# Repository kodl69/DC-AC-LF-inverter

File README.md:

# DC-AC-LF-inverter
software and hardware for modular DC/AC power inverter

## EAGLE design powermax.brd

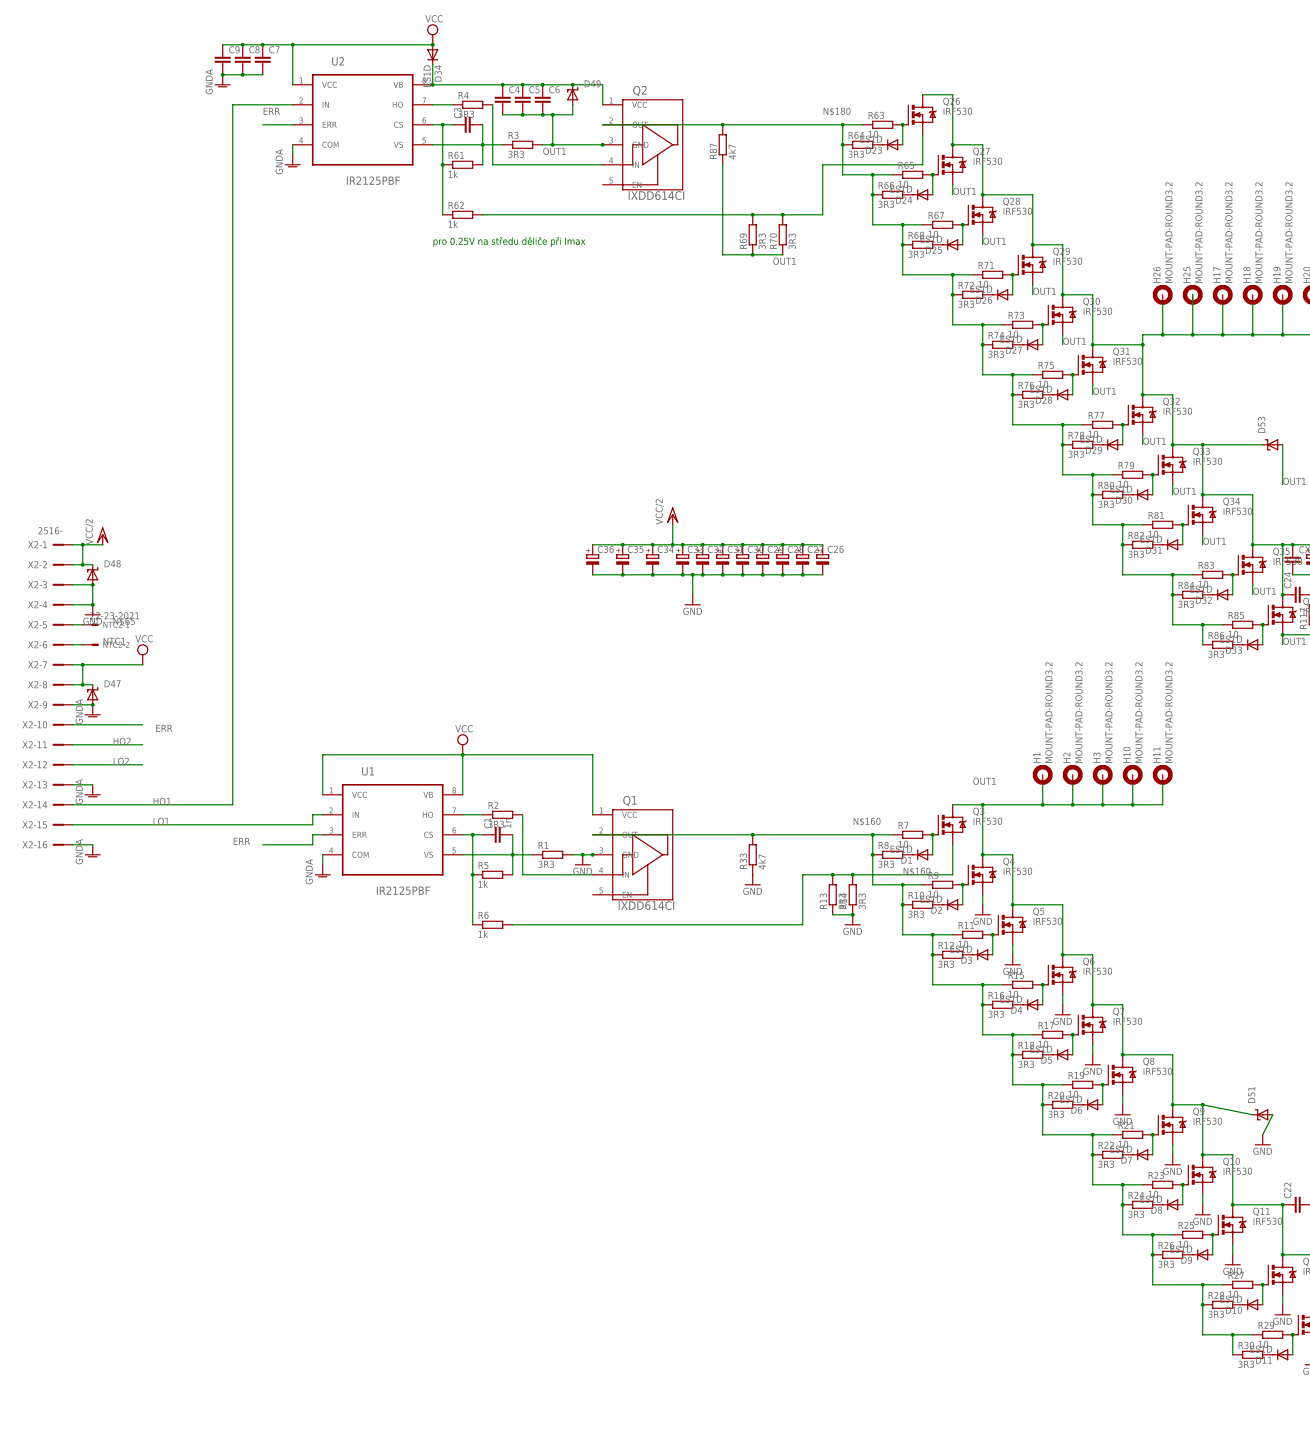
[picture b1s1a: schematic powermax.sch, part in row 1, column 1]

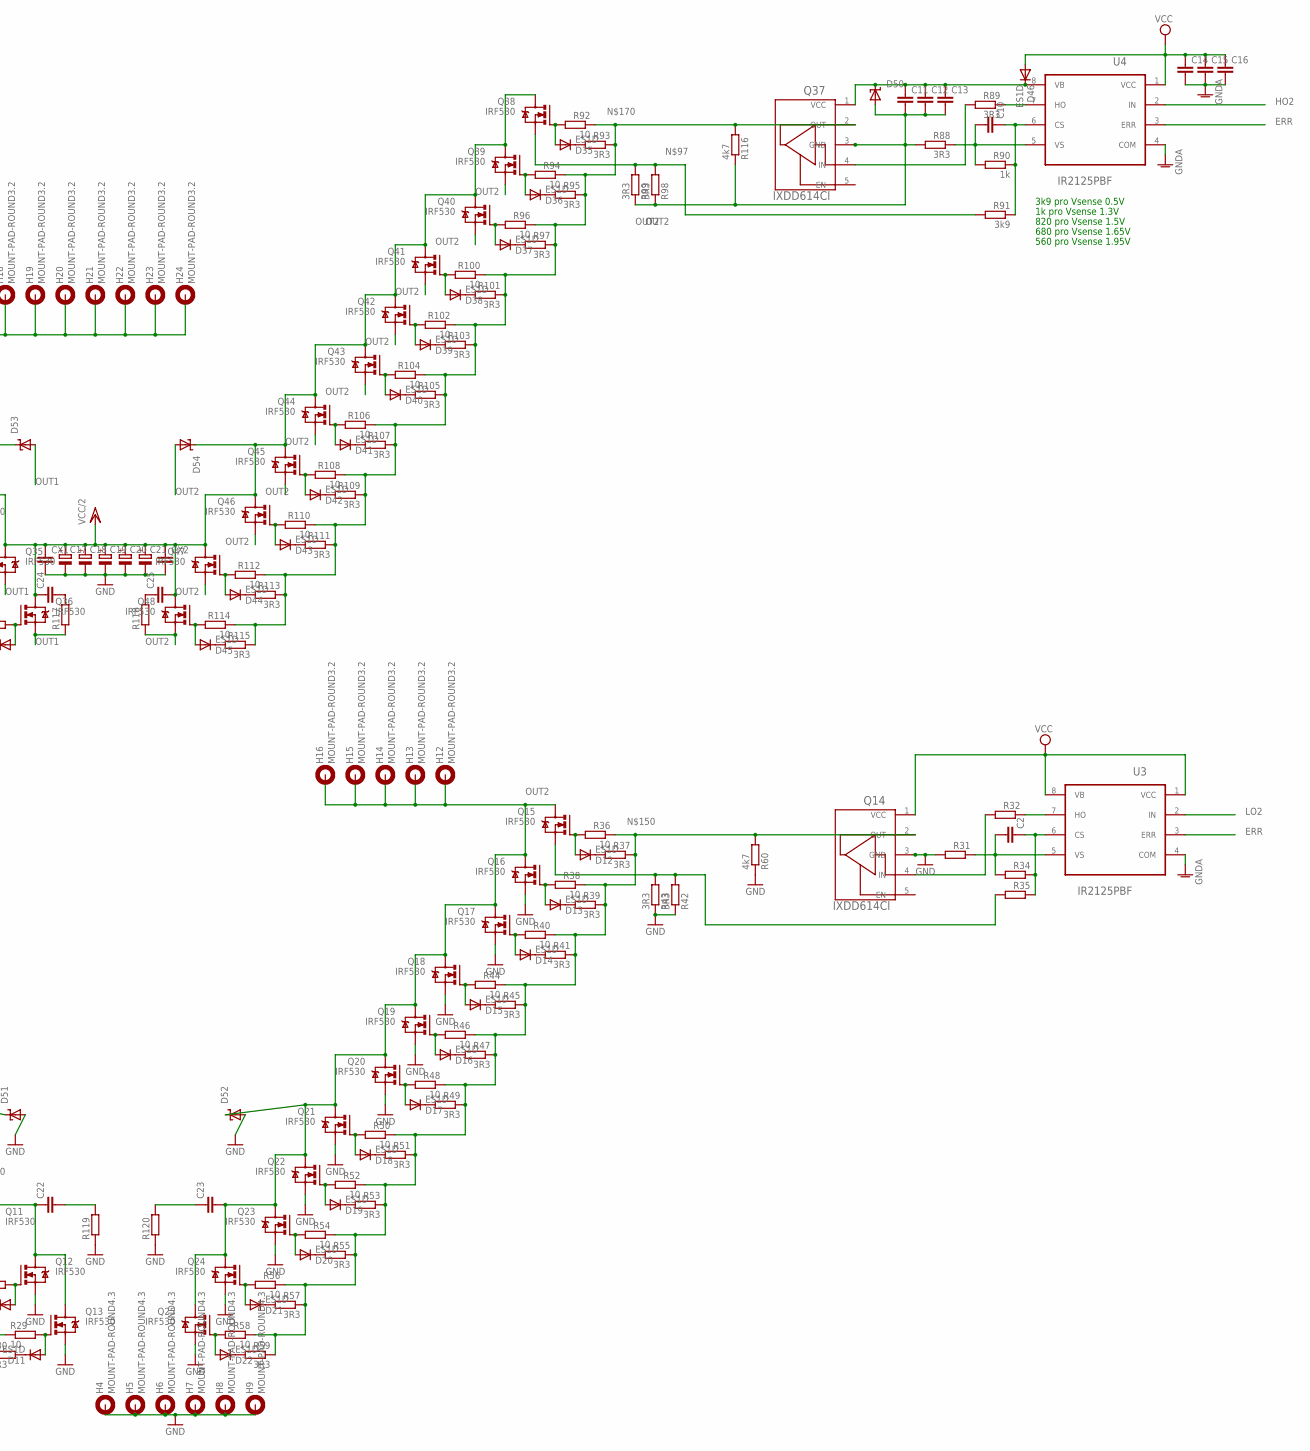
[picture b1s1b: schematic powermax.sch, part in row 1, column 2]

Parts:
C1: 1n; C0805
C2, C3, C10: C-EUC0805; C0805
C4, C5, C6, C7, C8, C9, C11, C12, C13, C14, C15, C16: C-EUC1210; C1210
C17, C18, C19, C20, C21: CPOL-EUE10-35; EB35D
C22, C23, C24, C25: C-EU225-113X268; C225-113X268
C26, C27, C28, C29, C30, C31, C32, C33, C34, C35, C36: CPOL-EUE7.5-18; E7,5-18
CX1, CX2: CXXC27B11; XC27B11
D1, D2, D3, D4, D5, D6, D7, D8, D9, D10, D11, D12, D13, D14, D15, D16, D17, D18, D19, D20, D21, D22, D23, D24, D25, D26, D27, D28, D29, D30, D31, D32, D33, D34, D35, D36, D37, D38, D39, D40, D41, D42, D43, D44, D45, D46: ES1D; SOD80C
D47, D48, D49, D50, D51, D52, D53, D54: SUPPRESSOR-SMBJ; SMBJ
H1, H2, H3, H10, H11, H12, H13, H14, H15, H16, H17, H18, H19, H20, H21, H22, H23, H24, H25, H26: MOUNT-PAD-ROUND3.2; 3,2-PAD
H4, H5, H6, H7, H8, H9: MOUNT-PAD-ROUND4.3; 4,3-PAD
NTC2: 22-23-2021
Q1, Q2, Q14, Q37: IXDD614CI; TO-220-5
Q3, Q4, Q5, Q6, Q7, Q8, Q9, Q10, Q11, Q12, Q13, Q15, Q16, Q17, Q18, Q19, Q20, Q21, Q22, Q23, Q24, Q25, Q26, Q27, Q28, Q29, Q30, Q31, Q32, Q33, Q34, Q35, Q36, Q38, Q39, Q40, Q41, Q42, Q43, Q44, Q45, Q46, Q47, Q48: IRF530; TO220BV
R1, R2, R3, R4, R8, R10, R12, R13, R14, R16, R18, R20, R22, R24, R26, R28, R30, R37, R39, R41, R42, R43, R45, R47, R49, R51, R53, R55, R57, R59, R64, R66, R68, R69, R70, R72, R74, R76, R78, R80, R82, R84, R86, R88, R89, R93, R95, R97, R98, R99, R101, R103, R105, R107, R109, R111, R113, R115: 3R3; R0805
R5, R6, R61, R62, R90: 1k; R0805
R7, R9, R11, R15, R17, R19, R21, R23, R25, R27, R29, R36, R38, R40, R44, R46, R48, R50, R52, R54, R56, R58, R63, R65, R67, R71, R73, R75, R77, R79, R81, R83, R85, R92, R94, R96, R100, R102, R104, R106, R108, R110, R112, R114: 10; R0805
R31, R32, R34, R35: R-EU_R0805; R0805
R33, R60, R87, R116: 4k7; R0805
R91: 3k9; R0805
R117, R118, R119, R120: R-EU_0411/15; 0411/15
U1, U2, U3, U4: IR2125PBF; DIP254P762X533-8
X2: 2516-; PAK100/2500-16

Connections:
ERR: U1.3 (ERR), U2.3 (ERR), U3.3 (ERR), U4.3 (ERR), X2.10
GND: C17.-, C18.-, C19.-, C20.-, C21.-, C26.-, C27.-, C28.-, C29.-, C30.-, C31.-, C32.-, C33.-, C34.-, C35.-, C36.-, CX1.2, CX2.2, D48.A, D51.A, D52.A, H4.B4,3, H5.B4,3, H6.B4,3, H7.B4,3, H8.B4,3, H9.B4,3, Q1.3 (GND), Q4.S, Q5.S, Q6.S, Q7.S, Q8.S, Q9.S, Q10.S, Q11.S, Q12.S, Q13.S, Q14.3 (GND), Q16.S, Q17.S, Q18.S, Q19.S, Q20.S, Q21.S, Q22.S, Q23.S, Q24.S, Q25.S, R1.2, R13.1, R14.1, R31.2, R33.1, R42.1, R43.1, R60.1, R119.1, R120.1, X2.3, X2.4
GNDA: C7.2, C8.2, C9.2, C14.2, C15.2, C16.2, D47.A, U1.4 (COM), U2.4 (COM), U3.4 (COM), U4.4 (COM), X2.9, X2.13, X2.16
HO1: U2.2 (IN), X2.14
HO2: U4.2 (IN), X2.11
LO1: U1.2 (IN), X2.15
LO2: U3.2 (IN), X2.12
unnamed: C1.2, R1.1, R5.2, U1.5 (VS)
unnamed: Q1.4 (IN), R2.2
unnamed: R2.1, U1.7 (HO)
unnamed: C2.2, R31.1, R34.2, U3.5 (VS)
unnamed: D2.A, Q4.G, R9.2
unnamed: C1.1, R5.1, R6.1, U1.6 (CS)
unnamed: D1.A, Q3.G, R7.2
unnamed: D1.C, R8.2
unnamed: D2.C, R10.2
unnamed: Q14.4 (IN), R32.2
unnamed: R32.1, U3.7 (HO)
unnamed: C4.1, C5.1, C6.1, D34.C, D49.C, Q2.1 (VCC), U2.8 (VB)
unnamed: D3.A, Q5.G, R11.2
unnamed: D3.C, R12.2
unnamed: C2.1, R34.1, R35.1, U3.6 (CS)
unnamed: Q3.S, R6.2, R13.2, R14.2
unnamed: D12.A, Q15.G, R36.2
unnamed: D12.C, R37.2
unnamed: D4.A, Q6.G, R15.2
unnamed: D4.C, R16.2
unnamed: D5.A, Q7.G, R17.2
unnamed: D5.C, R18.2
unnamed: D13.A, Q16.G, R38.2
unnamed: D6.A, Q8.G, R19.2
unnamed: D6.C, R20.2
unnamed: D13.C, R39.2
unnamed: D7.A, Q9.G, R21.2
unnamed: D7.C, R22.2
unnamed: D8.A, Q10.G, R23.2
unnamed: D8.C, R24.2
unnamed: D9.A, Q11.G, R25.2
unnamed: D9.C, R26.2
unnamed: D14.A, Q17.G, R40.2
unnamed: D10.A, Q12.G, R27.2
unnamed: D10.C, R28.2
unnamed: D11.A, Q13.G, R29.2
unnamed: D11.C, R30.2
unnamed: D14.C, R41.2
unnamed: Q15.S, R35.2, R42.2, R43.2
unnamed: D15.A, Q18.G, R44.2
unnamed: D15.C, R45.2
unnamed: D16.A, Q19.G, R46.2
unnamed: D16.C, R47.2
unnamed: D17.A, Q20.G, R48.2
unnamed: D17.C, R49.2
unnamed: D18.A, Q21.G, R50.2
unnamed: D18.C, R51.2
unnamed: D19.A, Q22.G, R52.2
unnamed: D19.C, R53.2
unnamed: D20.A, Q23.G, R54.2
unnamed: D20.C, R55.2
unnamed: D21.A, Q24.G, R56.2
unnamed: D21.C, R57.2
unnamed: D22.A, Q25.G, R58.2
unnamed: D22.C, R59.2
unnamed: C3.2, R3.1, R61.2, U2.5 (VS)
unnamed: Q2.4 (IN), R4.2
unnamed: R4.1, U2.7 (HO)
unnamed: C3.1, R61.1, R62.1, U2.6 (CS)
unnamed: D23.A, Q26.G, R63.2
unnamed: D23.C, R64.2
unnamed: D24.A, Q27.G, R65.2
unnamed: D24.C, R66.2
unnamed: NTC2.1, X2.5
unnamed: D25.A, Q28.G, R67.2
unnamed: D25.C, R68.2
unnamed: Q26.S, R62.2, R69.2, R70.2
unnamed: D26.A, Q29.G, R71.2
unnamed: D26.C, R72.2
unnamed: D27.A, Q30.G, R73.2
unnamed: D27.C, R74.2
unnamed: D28.A, Q31.G, R75.2
unnamed: D28.C, R76.2
unnamed: D29.A, Q32.G, R77.2
unnamed: D29.C, R78.2
unnamed: D30.A, Q33.G, R79.2
unnamed: D30.C, R80.2
unnamed: D31.A, Q34.G, R81.2
unnamed: D31.C, R82.2
unnamed: D32.A, Q35.G, R83.2
unnamed: D32.C, R84.2
unnamed: D33.A, Q36.G, R85.2
unnamed: D33.C, R86.2
unnamed: C10.2, R88.1, R90.2, U4.5 (VS)
unnamed: Q37.4 (IN), R89.2
unnamed: R89.1, U4.7 (HO)
unnamed: C10.1, R90.1, R91.1, U4.6 (CS)
unnamed: D35.A, Q38.G, R92.2
unnamed: D35.C, R93.2
unnamed: D36.A, Q39.G, R94.2
unnamed: D36.C, R95.2
unnamed: D37.A, Q40.G, R96.2
unnamed: D37.C, R97.2
unnamed: Q38.S, R91.2, R98.2, R99.2
unnamed: D38.A, Q41.G, R100.2
unnamed: D38.C, R101.2
unnamed: D39.A, Q42.G, R102.2
unnamed: D39.C, R103.2
unnamed: D40.A, Q43.G, R104.2
unnamed: D40.C, R105.2
unnamed: D41.A, Q44.G, R106.2
unnamed: D41.C, R107.2
unnamed: D42.A, Q45.G, R108.2
unnamed: D42.C, R109.2
unnamed: D43.A, Q46.G, R110.2
unnamed: D43.C, R111.2
unnamed: D44.A, Q47.G, R112.2
unnamed: D44.C, R113.2
unnamed: D45.A, Q48.G, R114.2
unnamed: D45.C, R115.2
unnamed: C11.1, C12.1, C13.1, D46.C, D50.C, Q37.1 (VCC), U4.8 (VB)
unnamed: C24.2, R117.2
unnamed: C25.1, R118.2
unnamed: C22.2, R119.2
unnamed: C23.1, R120.2
unnamed: Q14.2 (OUT), R36.1, R37.1, R38.1, R39.1, R40.1, R41.1, R44.1, R45.1, R46.1, R47.1, R48.1, R49.1, R50.1, R51.1, R52.1, R53.1, R54.1, R55.1, R56.1, R57.1, R58.1, R59.1, R60.2
unnamed: Q1.2 (OUT), R7.1, R8.1, R9.1, R10.1, R11.1, R12.1, R15.1, R16.1, R17.1, R18.1, R19.1, R20.1, R21.1, R22.1, R23.1, R24.1, R25.1, R26.1, R27.1, R28.1, R29.1, R30.1, R33.2
unnamed: Q37.2 (OUT), R92.1, R93.1, R94.1, R95.1, R96.1, R97.1, R100.1, R101.1, R102.1, R103.1, R104.1, R105.1, R106.1, R107.1, R108.1, R109.1, R110.1, R111.1, R112.1, R113.1, R114.1, R115.1, R116.2
unnamed: Q2.2 (OUT), R63.1, R64.1, R65.1, R66.1, R67.1, R68.1, R71.1, R72.1, R73.1, R74.1, R75.1, R76.1, R77.1, R78.1, R79.1, R80.1, R81.1, R82.1, R83.1, R84.1, R85.1, R86.1, R87.2
NTC1: NTC2.2, X2.6
OUT1: C4.2, C5.2, C6.2, C22.1, D49.A, D51.C, D53.A, H1.B3,2, H2.B3,2, H3.B3,2, H10.B3,2, H11.B3,2, Q2.3 (GND), Q3.D, Q4.D, Q5.D, Q6.D, Q7.D, Q8.D, Q9.D, Q10.D, Q11.D, Q12.D, Q13.D, Q27.S, Q28.S, Q29.S, Q30.S, Q31.S, Q32.S, Q33.S, Q34.S, Q35.S, Q36.S, R3.2, R69.1, R70.1, R87.1, R117.1
OUT2: C11.2, C12.2, C13.2, C23.2, D50.A, D52.C, D54.A, H12.B3,2, H13.B3,2, H14.B3,2, H15.B3,2, H16.B3,2, Q15.D, Q16.D, Q17.D, Q18.D, Q19.D, Q20.D, Q21.D, Q22.D, Q23.D, Q24.D, Q25.D, Q37.3 (GND), Q39.S, Q40.S, Q41.S, Q42.S, Q43.S, Q44.S, Q45.S, Q46.S, Q47.S, Q48.S, R88.2, R98.1, R99.1, R116.1, R118.1
VCC: C7.1, C8.1, C9.1, C14.1, C15.1, C16.1, D34.A, D46.A, D47.C, Q1.1 (VCC), Q14.1 (VCC), U1.1 (VCC), U1.8 (VB), U2.1 (VCC), U3.1 (VCC), U3.8 (VB), U4.1 (VCC), X2.7, X2.8
VCC/2: C17.+, C18.+, C19.+, C20.+, C21.+, C24.1, C25.2, C26.+, C27.+, C28.+, C29.+, C30.+, C31.+, C32.+, C33.+, C34.+, C35.+, C36.+, CX1.1, CX2.1, D48.C, D53.C, D54.C, H17.B3,2, H18.B3,2, H19.B3,2, H20.B3,2, H21.B3,2, H22.B3,2, H23.B3,2, H24.B3,2, H26.B3,2, Q26.D, Q27.D, Q28.D, Q29.D, Q30.D, Q31.D, Q32.D, Q33.D, Q34.D, Q35.D, Q36.D, Q38.D, Q39.D, Q40.D, Q41.D, Q42.D, Q43.D, Q44.D, Q45.D, Q46.D, Q47.D, Q48.D, X2.1, X2.2

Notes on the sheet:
pro 0.25V na středu děliče při Imax
1k pro Vsense 1.3V
3k9 pro Vsense 0.5V
820 pro Vsense 1.5V
680 pro Vsense 1.65V
560 pro Vsense 1.95V

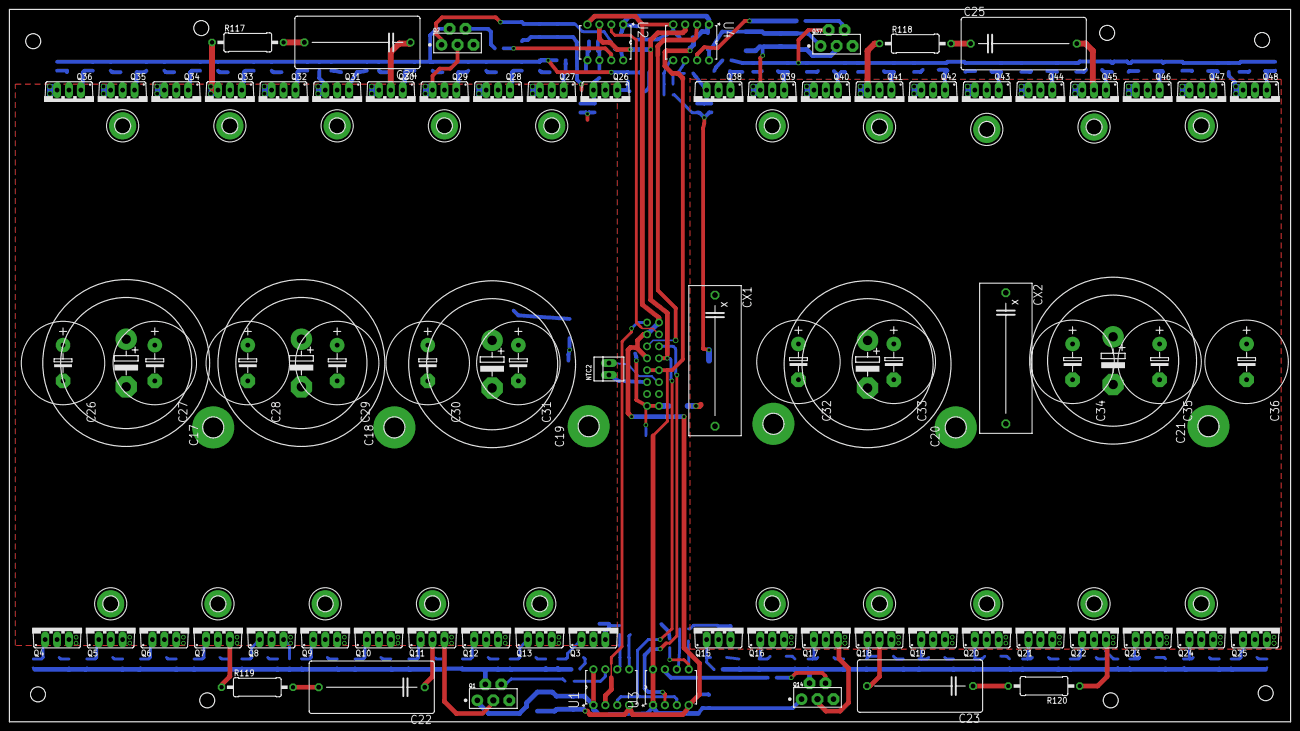
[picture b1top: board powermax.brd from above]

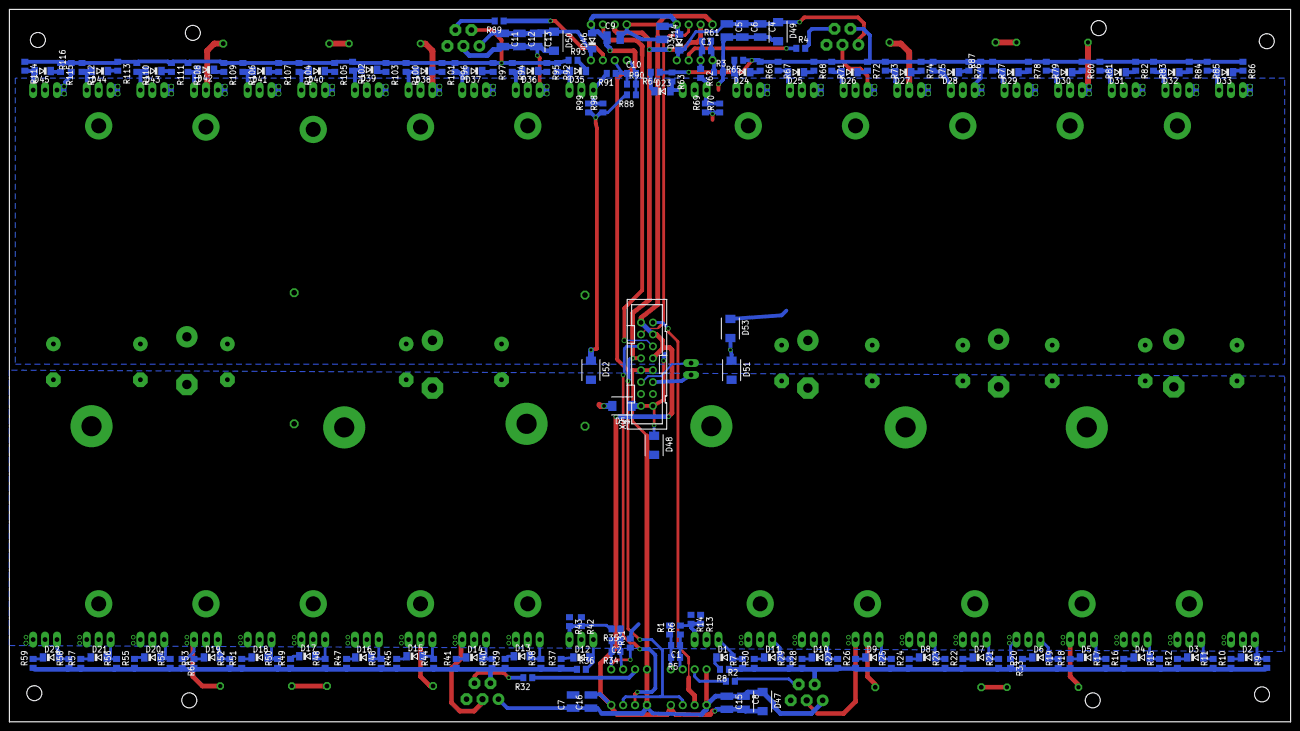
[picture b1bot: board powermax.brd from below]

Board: 2 copper layers, 273.0 x 151.8 mm, 292 parts (187 on the bottom side), 131 nets.

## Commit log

2020-07-16 Add files via upload
    first version, created in eagle 7.2.0
